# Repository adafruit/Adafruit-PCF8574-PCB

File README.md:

## Adafruit PCF8574 I2C GPIO Expander Breakout - STEMMA QT / Qwiic PCB

<a href="http://www.adafruit.com/products/5545"><br/>
Click here to purchase one from the Adafruit shop</a>

PCB files for the Adafruit PCF8574 I2C GPIO Expander Breakout - STEMMA QT / Qwiic. 

Format is EagleCAD schematic and board layout
* https://www.adafruit.com/product/5545

### Description

Expand your project possibilities, with the Adafruit PCF8574 GPIO Expander Breakout - an affordable 8 channel I2C expander.

GPIO expanders work like this: you have a board with some number of GPIO but not enough for your project - maybe you need more buttons or LEDs. You could upgrade to a board with massive number of GPIO like the Grand Central, or you could pop on one of these boards. Connect it over I2C and then you can send/receive I2C commands to control the GPIO pins to write and read them. It's going to be slower than direct GPIO access, but maybe that doesn't matter if it takes a millisecond instead of a microsecond. You only need the two I2C pins, and you can even share the I2C port with other sensors and devices. Heck, you can even add more expanders for massive I/O control!

The PCF8574 is a common, and slightly unusual I2C expander for folks who are used to the MCP230xx series:

* First up, its very affordable - who doesn't love that?
* It has 8 I/O pins
* Three I2C address select jumpers mean up to 8 expanders to one bus for 64 total GPIO added
* Each pin can be an input with light pull-up or an output sink
* IRQ output will automatically alert you when input pins change value
* This chip does not have a pin direction register. You cannot set the pins to be input or output - instead each pin has two possible states. Basically you can think of it as an open-drain output with a 100K resistor pull-up built in.
* Option one: Lightly pulled up 'input' - by default it will read as a high logic level, but connecting the GPIO to ground will cause it to read as a low logic level.
* Option two: Strong 20mA low-driving transistor sink output. This means the output is 'forced' to be low and will always read as a low logic level.

### License

Adafruit invests time and resources providing this open source design, please support Adafruit and open-source hardware by purchasing products from [Adafruit](https://www.adafruit.com)!

Designed by Limor Fried/Ladyada for Adafruit Industries.

Creative Commons Attribution/Share-Alike, all text above must be included in any redistribution. 
See license.txt for additional details.

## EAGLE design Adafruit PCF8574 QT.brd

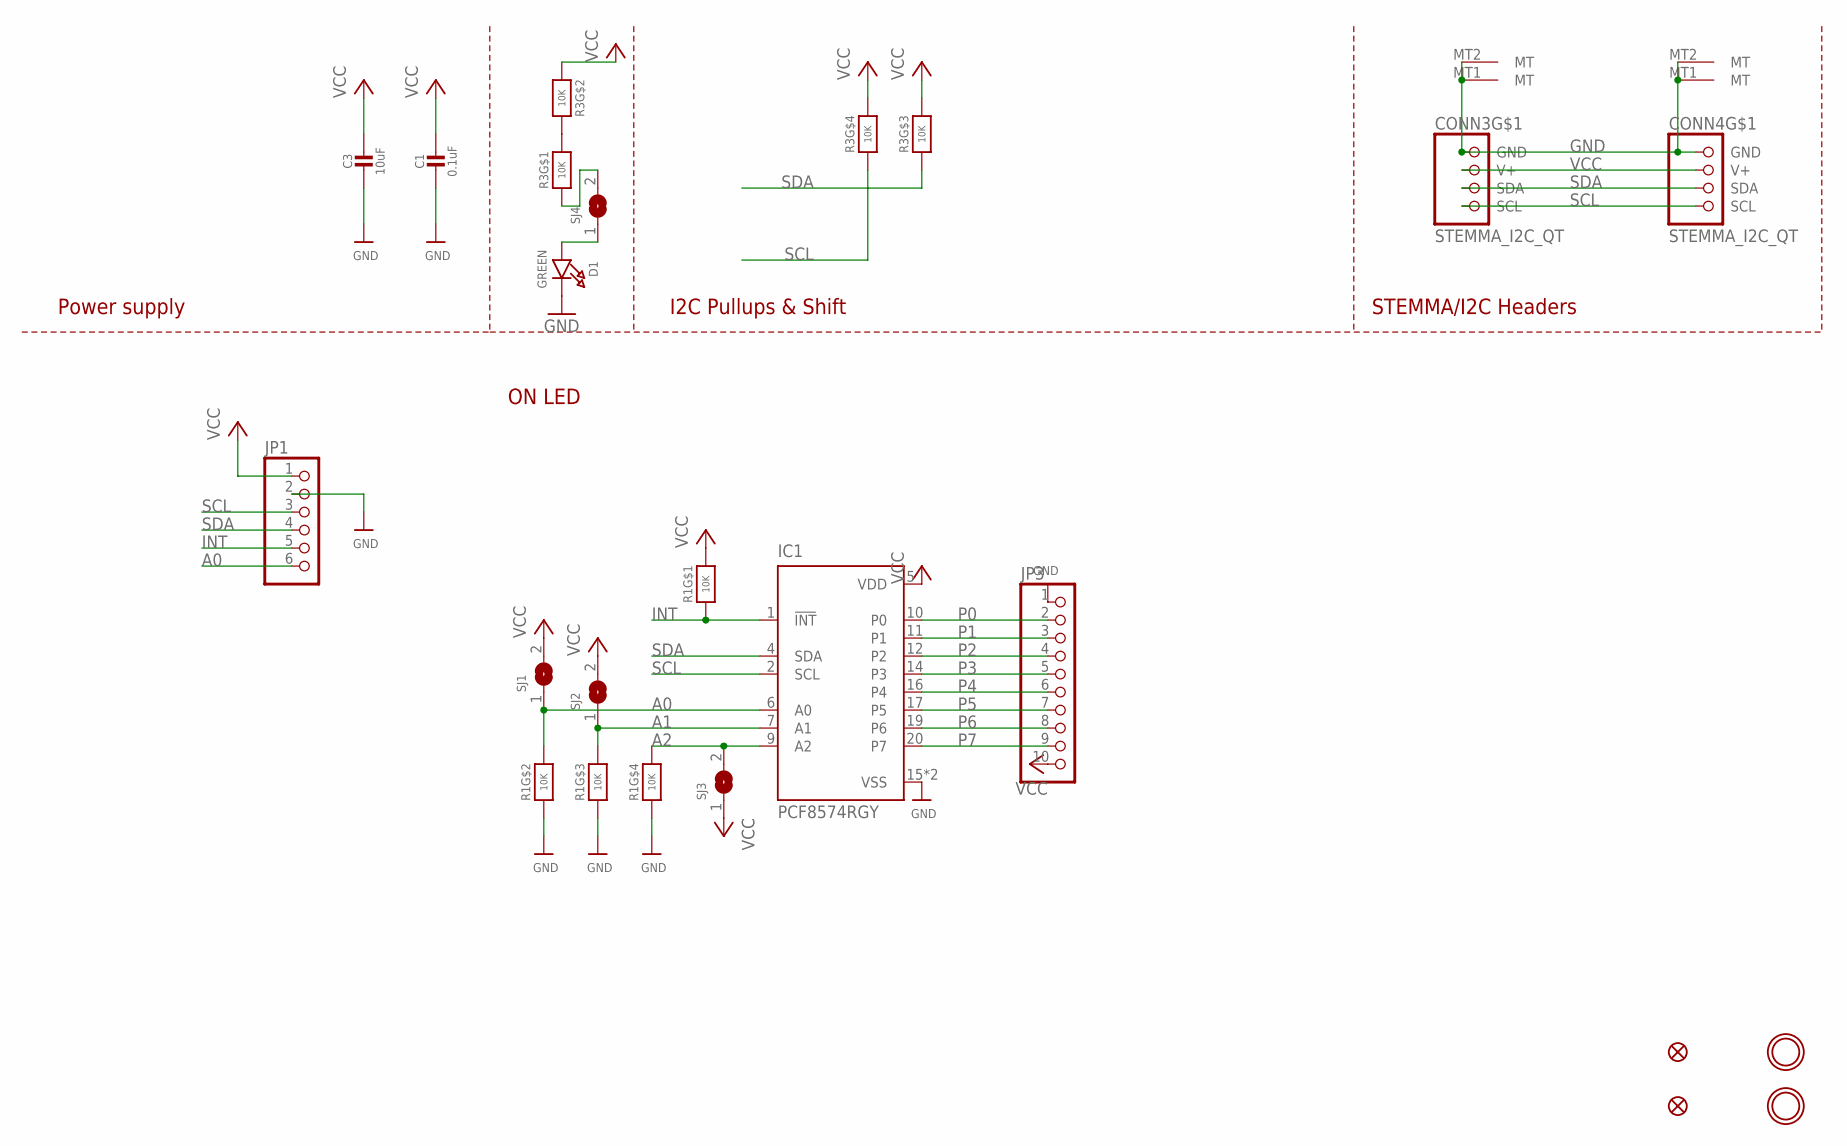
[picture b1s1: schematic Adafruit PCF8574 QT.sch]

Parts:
C1: 0.1uF; 0603-NO
C3: 10uF; 0805-NO
CONN3, CONN4: STEMMA_I2C_QT; JST_SH4
D1: GREEN; CHIPLED_0603_NOOUTLINE
FID3, FID4: FIDUCIAL_1MM
IC1: PCF8574RGY; VQFN20_3.5X4.5
JP1: HEADER-1X670MIL; 1X06_ROUND_70
JP3: HEADER-1X1070MIL; 1X10_ROUND70
R1, R3: 10K; RESPACK_4X0603
SJ1, SJ2, SJ3: SOLDERJUMPER; SOLDERJUMPER_ARROW_NOPASTE
SJ4: SOLDERJUMPERCLOSED; SOLDERJUMPER_CLOSEDWIRE
U$19, U$21: MOUNTINGHOLE2.5; MOUNTINGHOLE_2.5_PLATED

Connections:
A0: IC1.6 (A0), JP1.6, R1.7 (2), SJ1.1
A1: IC1.7 (A1), R1.6 (2), SJ2.1
A2: IC1.9 (A2), R1.5 (2), SJ3.2
GND: C1.2, C3.2, CONN3.1 (GND), CONN3.MT1 (MT), CONN3.MT2 (MT), CONN4.1 (GND), CONN4.MT1 (MT), CONN4.MT2 (MT), D1.C, IC1.15 (VSS), IC1.21 (VSS), JP1.2, JP3.1, R1.2 (1), R1.3 (1), R1.4 (1)
INT: IC1.1 (!INT), JP1.5, R1.1
unnamed: R3.1, SJ4.2
unnamed: R3.7 (2), R3.8 (2)
unnamed: D1.A, SJ4.1
P0: IC1.10 (P0), JP3.2
P1: IC1.11 (P1), JP3.3
P2: IC1.12 (P2), JP3.4
P3: IC1.14 (P3), JP3.5
P4: IC1.16 (P4), JP3.6
P5: IC1.17 (P5), JP3.7
P6: IC1.19 (P6), JP3.8
P7: IC1.20 (P7), JP3.9
SCL: CONN3.4 (SCL), CONN4.4 (SCL), IC1.2 (SCL), JP1.3, R3.4 (1)
SDA: CONN3.3 (SDA), CONN4.3 (SDA), IC1.4 (SDA), JP1.4, R3.3 (1)
VCC: C1.1, C3.1, CONN3.2 (V+), CONN4.2 (V+), IC1.5 (VDD), JP1.1, JP3.10, R1.8 (2), R3.2 (1), R3.5 (2), R3.6 (2), SJ1.2, SJ2.2, SJ3.1

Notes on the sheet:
I2C Pullups & Shift
STEMMA/I2C Headers
ON LED
Power supply

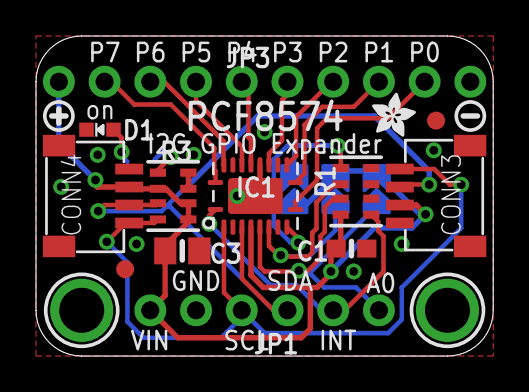
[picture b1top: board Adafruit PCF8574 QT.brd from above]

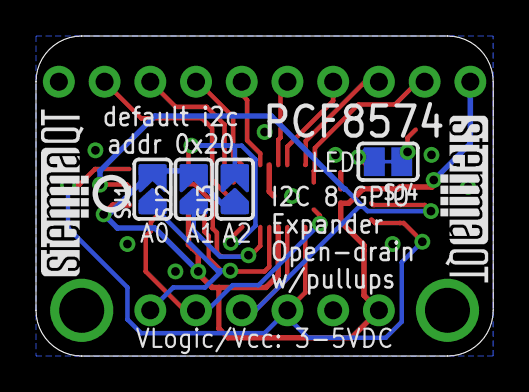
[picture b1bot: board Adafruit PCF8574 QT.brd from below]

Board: 2 copper layers, 25.4 x 17.8 mm, 24 parts (7 on the bottom side), 19 nets.

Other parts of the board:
U$8: ADAFRUIT_2.5MM
U$9: SYMBOL_MINUS
U$11: SYMBOL_PLUS
U$25: PCBFEAT-REV-040
U$30, U$31: STEMMAQT

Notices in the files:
parts and their libraries:
microbuilder: This work is placed in the public domain, and may be freely used for commercial and non-commercial work with the following conditions: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
